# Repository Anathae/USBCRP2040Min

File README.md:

# USBCRP2040MIN
Modified version of the Raspberry Pi (Trading) Ltd. RP2040 Minimal design 
example.

The original USB (B) Micro receptacle has been replaced with a USB C receptacle. 
KiCAD 6.0 has a foot print for the DX07S016JA1R1500 from JAE, and was used here. 
This receptacle breaks out the CC1, CC2, SBU1, and SBU2 pins, but only has the 
D+ and D- pins for USB 1.1 or USB 2.0 data rates. 

SBU1 and SBU2 are broken out, via bridged jumpers, to GPIO1 and GPIO0. CC1 
and CC2 are tied to ground via 5.1k Ohm resisters as required of a UFP for the 
USB C spec, and are also connected, again via bridged jumpers, to GPIO21 and GPIO22.

VBUS, as well as GND are routed to a second 1x2 .1 inch pitch header.

This is intended to be used for prototyping micro controller to micro 
controller communication over the SBU1 and SBU2 pins on the USB C receptacle. 
This does not impliment proper USB C DRP signaling, and may have problems 
acting as a host for other USB devices

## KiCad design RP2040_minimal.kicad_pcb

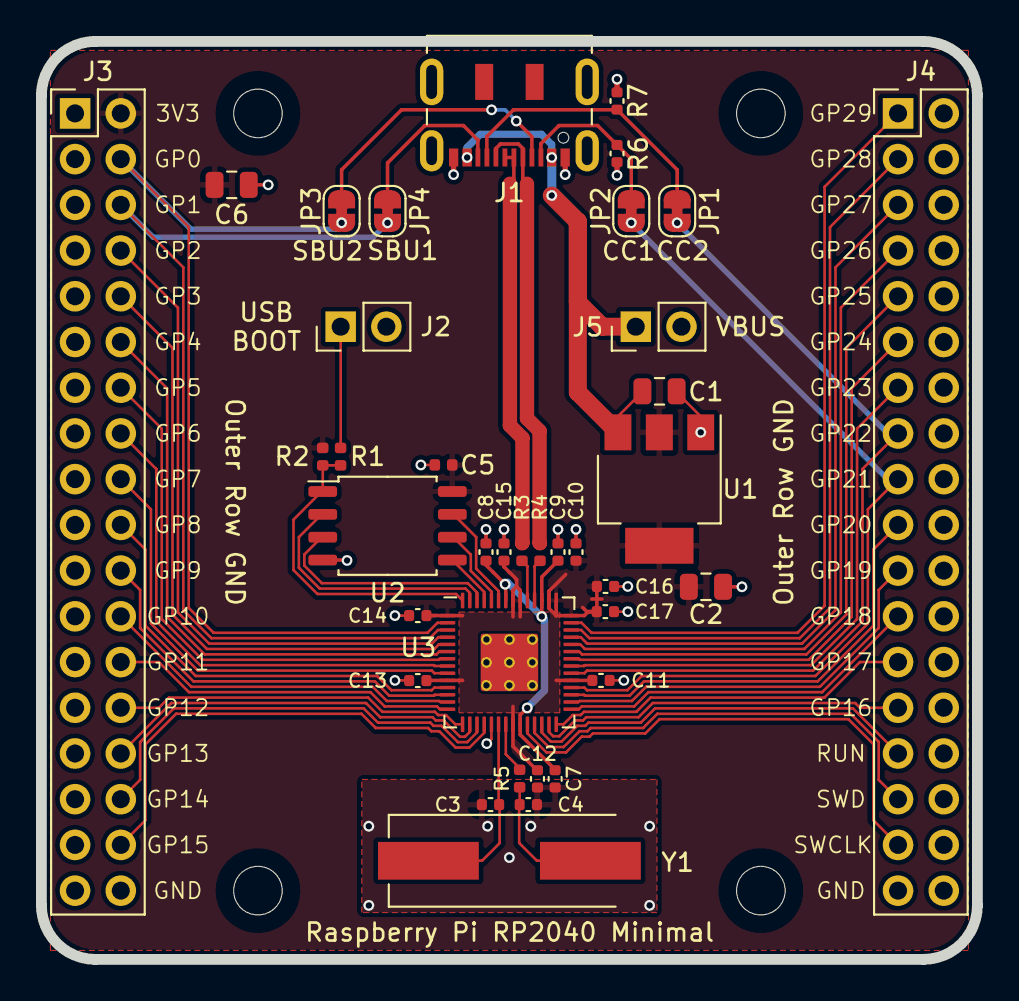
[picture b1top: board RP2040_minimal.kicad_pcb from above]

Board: 2 copper layers, 52.0 x 51.0 mm, 41 parts (0 on the bottom side), 55 nets.

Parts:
C1, C2, C6: 10u; C_0805_2012Metric
C3, C4: 27p; C_0402_1005Metric
C5, C7, C8, C11, C12, C13, C14, C15, C16, C17: 100n; C_0402_1005Metric
C9, C10: 1u; C_0402_1005Metric
H1, H2, H3, H4: MountingHole; MountingHole_2.7mm_M2.5
J1: USB_C_Receptacle_USB2.0; USB_C_Receptacle_JAE_DX07S016JA1R1500
J2, J5: Conn_01x02; PinHeader_1x02_P2.54mm_Vertical
J3, J4: Conn_02x18_Odd_Even; PinHeader_2x18_P2.54mm_Vertical
JP1, JP2, JP3, JP4: SolderJumper_2_Bridged; SolderJumper-2_P1.3mm_Bridged_RoundedPad1.0x1.5mm
R1, R5: 1k; C_0402_1005Metric
R2: DNF; C_0402_1005Metric
R3, R4: 27; C_0402_1005Metric
R6, R7: 5k1; C_0402_1005Metric
U1: NCP1117-3.3_SOT223; SOT-223-3_TabPin2
U2: W25Q128JVS; SOIC-8_5.23x5.23mm_P1.27mm
U3: RP2040; RP2040-QFN-56
Y1: ABLS-12.000MHZ-B4-T; Crystal_SMD_HC49-US

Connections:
+1V1: C7.1, C8.1, C9.1, U3.23 (DVDD), U3.45 (VREG_VOUT), U3.50 (DVDD)
+3V3: C2.1, C5.1, C6.1, C10.1, C11.1, C12.1, C13.1, C14.1, C15.1, C16.1, C17.1, J3.2, R2.1, U1.2 (VO), U2.8 (VCC), U3.1 (IOVDD), U3.10 (IOVDD), U3.22 (IOVDD), U3.33 (IOVDD), U3.42 (IOVDD), U3.43 (ADC_AVDD), U3.44 (VREG_IN), U3.48 (USB_VDD), U3.49 (IOVDD)
/CC1: J1.A5 (CC1), JP2.1 (A), R6.2
/CC2: J1.B5 (CC2), JP1.1 (A), R7.2
/GPIO0: J3.4, JP3.2 (B), U3.2 (GPIO0)
/GPIO1: J3.6, JP4.2 (B), U3.3 (GPIO1)
/GPIO2: J3.8, U3.4 (GPIO2)
/GPIO3: J3.10, U3.5 (GPIO3)
/GPIO4: J3.12, U3.6 (GPIO4)
/GPIO5: J3.14, U3.7 (GPIO5)
/GPIO6: J3.16, U3.8 (GPIO6)
/GPIO7: J3.18, U3.9 (GPIO7)
/GPIO8: J3.20, U3.11 (GPIO8)
/GPIO9: J3.22, U3.12 (GPIO9)
/GPIO10: J3.24, U3.13 (GPIO10)
/GPIO11: J3.26, U3.14 (GPIO11)
/GPIO12: J3.28, U3.15 (GPIO12)
/GPIO13: J3.30, U3.16 (GPIO13)
/GPIO14: J3.32, U3.17 (GPIO14)
/GPIO15: J3.34, U3.18 (GPIO15)
/GPIO16: J4.27, U3.27 (GPIO16)
/GPIO17: J4.25, U3.28 (GPIO17)
/GPIO18: J4.23, U3.29 (GPIO18)
/GPIO19: J4.21, U3.30 (GPIO19)
/GPIO20: J4.19, U3.31 (GPIO20)
/GPIO21: J4.17, JP2.2 (B), U3.32 (GPIO21)
/GPIO22: J4.15, JP1.2 (B), U3.34 (GPIO22)
/GPIO23: J4.13, U3.35 (GPIO23)
/GPIO24: J4.11, U3.36 (GPIO24)
/GPIO25: J4.9, U3.37 (GPIO25)
/GPIO26_ADC0: J4.7, U3.38 (GPIO26_ADC0)
/GPIO27_ADC1: J4.5, U3.39 (GPIO27_ADC1)
/GPIO28_ADC2: J4.3, U3.40 (GPIO28_ADC2)
/GPIO29_ADC3: J4.1, U3.41 (GPIO29_ADC3)
/QSPI_SCLK: U2.6 (CLK), U3.52 (QSPI_SCLK)
/QSPI_SD0: U2.5 (DI(IO0)), U3.53 (QSPI_SD0)
/QSPI_SD1: U2.2 (DO(IO1)), U3.55 (QSPI_SD1)
/QSPI_SD2: U2.3 (IO2), U3.54 (QSPI_SD2)
/QSPI_SD3: U2.7 (IO3), U3.51 (QSPI_SD3)
/QSPI_SS: R1.1, R2.2, U2.1 (~CS), U3.56 (QSPI_SS)
/RUN: J4.29, U3.26 (RUN)
/SBU1: J1.A8 (SBU1), JP4.1 (A)
/SBU2: J1.B8 (SBU2), JP3.1 (A)
/SWCLK: J4.33, U3.24 (SWCLK)
/SWD: J4.31, U3.25 (SWD)
/USB_D+: J1.A6 (D+), J1.B6 (D+), R3.1
/USB_D-: J1.A7 (D-), J1.B7 (D-), R4.1
/XIN: C3.1, U3.20 (XIN), Y1.1
/XOUT: R5.1, U3.21 (XOUT)
/~USB_BOOT: J2.1, R1.2
GND: C1.2, C2.2, C3.2, C4.2, C5.2, C6.2, C7.2, C8.2, C9.2, C10.2, C11.2, C12.2, C13.2, C14.2, C15.2, C16.2, C17.2, J1.A1 (GND), J1.A12 (GND), J1.B1 (GND), J1.B12 (GND), J1.S1 (SHIELD), J2.2, J3.1, J3.3, J3.5, J3.7, J3.9, J3.11, J3.13, J3.15, J3.17, J3.19, J3.21, J3.23, J3.25, J3.27, J3.29, J3.31, J3.33, J3.35, J3.36, J4.2, J4.4, J4.6, J4.8, J4.10, J4.12, J4.14, J4.16, J4.18, J4.20, J4.22, J4.24, J4.26, J4.28, J4.30, J4.32, J4.34, J4.35, J4.36, J5.2, R6.1, R7.1, U1.1 (GND), U2.4 (GND), U3.19 (TESTEN), U3.57 (GND)
unnamed: C4.1, R5.2, Y1.2
unnamed: R3.2, U3.47 (USB_DP)
unnamed: R4.2, U3.46 (USB_DM)
VBUS: C1.1, J1.A4 (VBUS), J1.A9 (VBUS), J1.B4 (VBUS), J1.B9 (VBUS), J5.1, U1.3 (VI)

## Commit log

2023-05-05 Update README.md
    corrected initial text
2023-05-06 KiCAD project files in https://datasheets.raspberrypi.com/rp2040/Minimal-KiCAD.zip
2023-05-06 .pcb and .sch saved as version kicad 6.0
2023-05-06 Prettied up the component and route placement.
2023-05-07 Moved processor, flash, crystal and associated passives towards bottom of board.
2023-05-07 Deleted flood fill for VBUS, tightened up passives for 3.3v regulator. Moved 3.3v regulator towards processor.
2023-05-07 Turned off visibility of User.Drawings layer. Used for centering references.
2023-05-07 Updated sheet information, renumbered annotation for capacitors.
2023-05-10 Replaced USB Micro A receptacle with USB C Added 5k1 resistors for UFP identification Added jumpers connecting CC1 to GPIO21, CC2 to GPIO22, SBU2 to GPIO0, and SBU2 to GPIO1. Added jumper for VBUS
    Updated README.md
2023-05-10 Really updated README.md this time.
